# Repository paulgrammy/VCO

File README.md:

# Thomas-Henry-555-VCO
VCOs or Voltage Controlled Oscillators output a signal at a fixed amplitude but variable frequency depending on the amplitude of the input voltage. 

In Audio, VCOs are used as bases for Synths and Modular-style music that is commonly paired with the Eurorack standard. The Frequency domain of Audio is 20-20k Hz.

This repo is based on the Thomas Henry VCO: 4 Waveforms, clean 1V/Oct, Sync, PWM modulation and External FM.

# Documentation
"VCO's of different designs, can sound different from eachother despite them producing the same basic waveforms. This difference is not really that noticeable if you listen to just the basic wave outputs. It starts to become more noticeable when you start playing with the Synchronization and the Frequency Modulation inputs. That's where this VCO really shines and I think that's why it is so popular in the modular synthesizer world. With the Hard Sync and FM functions the VCO-555 produces a very full sound, rich in harmonic content and very musical sounding. And it tracks very well over the octaves. Plus it's very stable with the PTC installed for temperature compensation. You'll find out once you build this module and start experimenting with it. It's the VCO of choise for many hardened Modular Synthesizer aficionados." Source: Eddy Bergman

This project mainly used the findings from Mr. Bergman found [here](https://www.eddybergman.com/2020/12/synthesizer-build-part-37-thomas-henry.html).

# Simulation
[Falstad](https://www.falstad.com/circuit/circuitjs.html?ctz=CQAgjCAMB0l3BWEBOaB2AHAZmcjAWBLANgwCYwsRjkQl8qEBTAWjDACgw19w1i+AsMjIgy+SFHDw4UWJCQBRABoAFEADEAsiACCAF31MAdgFcAhvoCWAe2McA7uBFjIGMeNfvIHAE4feMjcAkCxIXkkwGR8nbiF+cDBROKgOILRweIFIhN4VVQAdAGdtLh5E0TI0ZLJ3LBIpKJk5LAwk6I7wkABhAHldACUAZUUOAHNBMQlJsgRs1PTM0K7JMN5ePsGRjgGKsWq92fnJabAkSQvoBB29+qEk0IRRC5BptnOpGGv-JLqusk8a0a0T84FqrzAAgB60hUnqIN27FE+Hw7iRr2IESkbzOnzk10RD1avHRJG82MiH0u10WsPwsJOdM0AEkAHKjbgkokEMHuFHkprwOSIFnsxwhelQwErcXQiFS3hPbyguVK3l0cGREGxcFq9Fqny0gQGjV88AANWKAHpir1ugAVFWeNWqlxakHmfbIzGhHn4H1opDvaTREBoWBkTFVNCQAFYTDiVgZd3wWXTfliOavVGpJxHbPufMSC4qrPF33rWSSIJwWVlnNVZE5mJe14Yatl9upCZFrv5hAPEtOYmvWQj-0RMq8cc+8sIFHAy54AedGQQc0gK0gO32kD23xWAC2oJHc1WXTPcOQPh7B3ngTvxBeLbnDwndEH4vfA+9vGInhfZABGIMsgNCBoWzVMllmnUhcxg0I4KBfMfH8ZCsxHFDXhjFtMMBHkUlQitJiBQjwAQWsJlIhJkOCEs0II3IuzIwUfF2VEcgEfAwLIk5KTxL4OAkJtCyzS98wgSBiikooJGKd5pMUoovigJS5KKM4lJklSZLAeSzmgLAEGwBA8ExekKEjaSriwWYznEGNUTwBRiiaYoABMmAAM3MUwABt9FUjT5K+WyByefBHIwZyEGsogASffAAXYYh-wwNBXLgDzvN8gKgr05S4tsyNwmSyE0oyjSsqKTyfP8wLdP0sBoGcoyEH4UzanqSrQoBdqMGwVpryqTKZNq3KGtc-T8HQBRxGQBA5nECR0v06AkqwShFshapCDOZBRuyuq8pktgir62phDAJK3GEEKbOEZA0FwZ60rAVaqrGnL6qCs7CqKFhQse56nqAy6PrcmrvpO-TiiqaB0rONxIsxN78Hu+LZku5BrqCNoDs+o6Jt+gqYGugdyBjLBIrITbqawe7roW4g0GqenIHjPAGcJqHjsmgHScZ7i5lZ2mGA557sEO3nidOgqZqjYgwh4SAQPF7nAegcn3qqDmabphhpfGn7Gv+oHcDIZAbqINpKsh42YeCgHeoc-gGEwf08CKx7Let1puCN6H+YKlhaZarnMCSJ8ojQAPlJs6FWcxeMCBoDBA75-KlLYFrFpwanISAln-2IDPZam-6c9IeLhFS9L3ci1h055h39HFPD1lskIXy7uUGEqAb4P7sRB4zWplWHHl80w6ZcKn9MG1nr9F5OBsAPFe8QnahV4O3reEnH3eaIabiBDuXen0zYDPBQ8YC1bDMgSHe+iwbA4iMwjCeVsl4kZvYif4AIgqkSESAQJcS7izZEkDQhXAwBRWoqNyA402qwJIHBPRQOcKINATxsEoHIiAYMrFZBRFgP+Cm6QSrIE2tIchkZ3rYGWmELoJC0yr0LOmBk7D5QSm4U4f8gQsyCMmC2ERKQsGEQ4AAY2oDfYRN9B7VmgGQVgtAyGqwYQNWyKIWERHkJwCYIjD4iKfkfKEg897nzEQcPG1BbFLwEQ4yQ1RqyOLDHBcQLi4LCGeOKfgaIXC4OSG6fxQQpguPCYAlsriIkeM4c-AJ+CcYhL8Z6FJXgUAuDseooMuISFanofSdqUQlazAUHQzRlDIDVCfDQiAbCnAZLlNFHeLZWkhA6Y2VI-gukHCYa2FMRE+miA6dY1wqZelgW6RbQZEzaxNOyQcWZdi2IgAGd0toUJ34UkIc+K4d8xkNDGXg+iWTKgHCiIPbp1ZJnSGuZctwdRgE1n-lc55QgnmPGePBd5rZKALhuRwXo4BqYPmSCQasOzDQ1NBYC04tkEmvD3AMZkuhWQAHEAAyoxFkXNELM8sLZXSiDVJ1XeuoXBqmCfBbpm8gSb1wheBcDLL4+ECtBUxcFwFSDYMKeAkYJArWpjQHgkYeSaxRoQGpeByAohoCGEArcOCBXfCItVWYIB8soAjZ6ZxUTCGpk8SAWrerGs2hzSgIFnqKuVU4Di1BQLASzC+WEPLh48p7qId1OZPWgklI6risJYnVleTI3hsTz4hvAGg5RmJwjU1wVEdqaBWj8s4MOBokaGikAnuBYCg9z5+rQjmh53qlHkQRK2XNV9qAVr4kQ3E+zrjDm5Yo9wIj-4mPbdQWeqR3IRvCafMM4TRDKs5K8MCsTh1JKGZcWmutVwCpAAACQ0HuA8x4nA-jDHg6lpy74zr9GBdsz4MH5viRGuCgZG1IAKUQmAMhBXhDcCKp6SVSBYkacRd1bqXVfmDXBANIb25ZqiVmg9VEugewQqez4oHnVnzwcWi9sTunRoKbKA4sTfEjpLBOiRg9cM0rnfypAWK2SaB0AYIwZhLC2HsLIwjaIEjxqkGQLWuAuPcZ4xgJM-LIA8aE7gJ4yYDHigkacB4bGYUZDdX2tjvAKOsmKKUCYKQaUabgs-IEMGo08kAgIAZQIBkfy6AQJFFnFyplkV49ZXcUimdeOgWN6b00SYSAM9EpmVWTqM13S8TmtXXXDlxogJrUSUyoI+mQhA5glNSvOSgqbFq2qDhwAdw6BonBPb3JV6WJhZa7FlsCJYJiBZzIF0rF9JBbLoJfODkEGuyEvDBoirWeStfCScHCNwuuSFaysXZTbPgHIEcENjT53B1bEcEOrgXuG7GnbISNBnhtUnxHfGl5KaVTfg04GD744PvnabII7sgZPijg5Nib7ioLXq7tBdpj2HvIlK1druR71jvYEWJcEe2DTigB-94IRk-HjbqHgyNB6DtRKh1E7rQPghqgB2ypH7hLxscvGI6Y5K2NWZ8LImtePB6dpjSwWgqBhPCfOOJgRlignhPJf-GtIjWcuvgopn0bHrFA+mOfDAPpedOEF9OY5s5mxXYl+4DJGZZsY8vgD0Jv3jSK9x2jgRuOXBK-B72k43Oyw+lk0sJzAzeArsGAAEWKEMAAmqybooJ8c5hpQTkMqYDt4Ks67qsoIfeSBrY1ytdz-e7pwcAzD-hQ91aD9+0XcjeDx8a1d2EcGk++4nbExyl7U3zBIfiXAS74AQAGLoLQ6huh2GMEwaRgV9xHhuDB7PcHs8vBxBtwSS3wnZ570NhtI3qQ3EDxd-pVZdnBmbee13AYZ+J8IcQjoD75ACqqBRaKltWYmrCHn7U6zZ978T77iYruuyu+q8S6YVm7M+eHOZnMJmu4+HSW+H0hLX-z-yYvmLsZLaLQoP6eMFmcgCCZfAEaoLZA1AEOAeBNEEEXpbnTwePOXd3FsWXLsDJRlUEDAhcDJMnVicUXAxAhAycfwbA3gWZRlFAggqlHAlwE7LAugn0GOX8azCTGpFggFdYI3NIWFTg14BzRFfg5EEAUvcvYFOFLgkkSFDELEVAug0hdg0cZ+ZgpQ6QA4TtISWMaQLMTTSEdwTTIKGSdSBSM2OKQw4odSTSUw+Oc4CuNgLAFRGMK2ecUgJWDmWMOKaKQTdsbAcgE1VmdGFuIOLOZ2OBa8ZyXwoIbgHgTwgafuFw6mAgO6IIzOU2bSOBOIsKAA1EekAme2YI02ewhGBQHAFEbgcePAAmL4fGZwtoX2J8GpMuE2OwnVaKdsVobeH-WOMgOKAcdgTaEQHGf0Z6bmfI1I2GGw-GaKPo+MSFSgDGW2EVZBdqSLZuMY8uAWbOao7gJY3-HgAaNY6qVuEmOGcMKBOYTkZwumZuTWYyYQaY-o3PLfJox2P6L4Po26I4QgauEOd4tweKLmTaJ8UYo4goiY06P4+BWyQEyEDmF4-mP6AyYyBaIyAgX-UyWKUI7aK5JIOYb4+BAqdY5op2dIu46oICLaJWVOQk0E8Yp2W4qYlED9AcEQYgUmOBcoikoyKk-0Gkr6OkkOJILWFETAQXAJCiXATw+4pkyMFkhheEkIiE2AMIAaSgbREGCgeoEE-kjYwWf6IkgKNgibLMICAPf9JpRXLMDpP1EXMCHlDpEQZUH4aAwNEMfQ05FAoiZNRDRIZDDneEBZN0107010r0l0mlK2XgEjT0nwCdR0vDFAcEWdT0uQRsFhIvXgIYNkRQEAIYAAT0PEPCYH0F8DzI3Qb12HjNiSrL71HD2VGwJETP0J5HjKDwbQnwbNBCaHdOSBdKcxYTvm7Ps17Lm2bF+XDLwSiGmBIzYOnMnJfTDAM1nJcQIgUAEDa0HLXITJDJrTK20PXPnKtIZB6V9JwQInsnWTHPwJ+AvKsz+Td0XRbHYHh0iHeijMR1iDfO3K-I3M-Lgk0xrDD3HPUM8B3PXliC3PEUgvNLBBW0nMAptNgrNPuD9OyAkx-PPKhyXJ+EAoAtkDdwDNrERC+TvMULd37w7wOUREArvJoqN3WwEgOUCiSBPVIUtn82SHAEbWIGgBoCZlqRoHqFpmyHWmvCSBIGLn-Eljk1kGVWYs2lGQEIeHjwaUbXDHekhCCBoUIFNPjDkDqW4n9jfOvFRDvVkvSx1FYsiHYqAqfMEJUrBQP1+UcocoXFbwkxspUvEGm24J1C7C828uHN+UCq8pzB82orCocwXSCrb34knx1DgpqCnQPR+Ecuz1+BcSG0XRuAyrDFYUFTytkLrI7MHz8oGxcD4OZ3EMqoqukOZwWF4McsvEoF1EvkzOzMHMcsPj4LMSwC7K6qIy6p2UFAkzStYUcqwTsoXEkVqAD3fg8q7Bmq7CqtSoXAdT4JO3d06rWuYkcuHVWH6umuCBqp+RGvUwmuOomoAlCB4LkwEEjKkAet4FUAAHUtAPN7qFx0QHqnyXAnod5-qQFygUgHrcMhzSMYskBXrqNDATALBrA7ApxJgVCwarVrMqx1pEoi84AqA2RmR7Q0UsUQBVAABVLFEYEAF65kS3e0FdCTCqqckIdgGUWIBIFGh4FQ43WETmtQ4Qtke0YoQoIoKmmmumxENmtGlIZ8n5dsgfTbcWz5S5Nmrc2K+swfdTZW465W66oiOUQGwBQGudJ0LkLoQBZmrEQi3CcJc20Ia22MScT0aCKcjhaQS-D-My0Mb-OACQTkWOekSKekDS9Gq2rUQEcJQ29uHxe2220Oyce1Jghc98COtCcO3IV-BIaymQO+MHfc75RIPvduQ8s+KOmCjMZ2mQ12ksT0PUBcqC6YXJW9GMpfH2ngP266HgdgdsMylRe8QTbiQXH+BgT00EbLJsj8AlTUDwQM0e1ssCeM9rB4QGkRQ2qerO7dcEKIZ0Dm6OyCbereglDOjeRehIHdeeoHUC2uzwCO+OkkROhO0u++40DelWp3K+zzOejO5YWsKZe69+z5Ptd6SidZHiBcjpG25+B0tmwQiO868EWZFq2AuiG61KuB2quBz+ka2kaBr6hSlANa4msm7YEFBBlAKBnAz+nwGwKYKgSSciDSiAWnOAChdjahm6qhhyLiykeh6QflZhiASoSKNhqYdRRoCmdgOgXh2YMQaR+aIR7q0R7hxhqpUIGRwtDgIAA)

# Schematic
[555 VCO.pdf](https://github.com/user-attachments/files/27636569/555.VCO.pdf)

# PCB Designs
V1:

V2:

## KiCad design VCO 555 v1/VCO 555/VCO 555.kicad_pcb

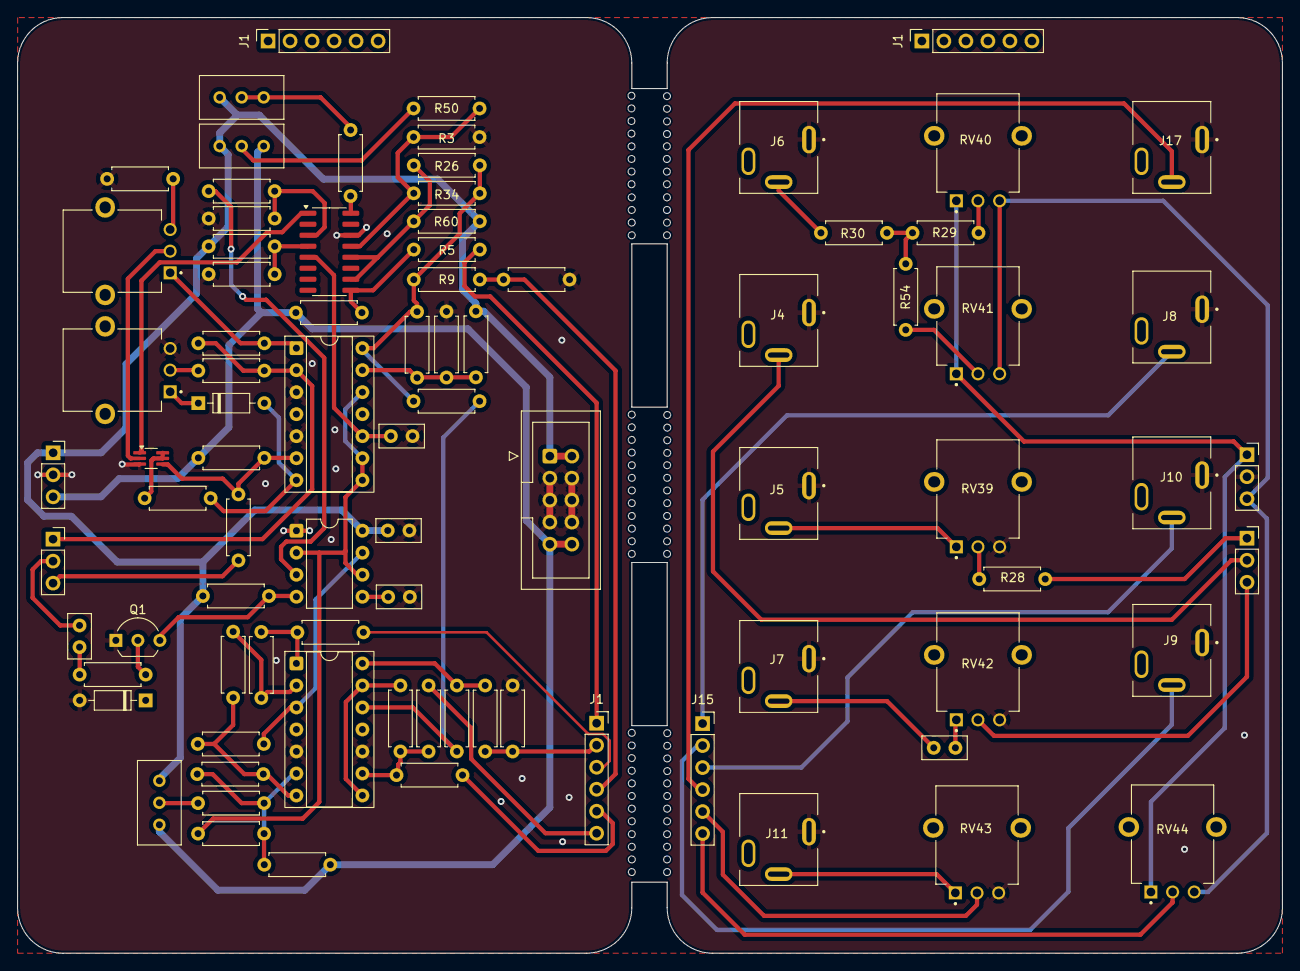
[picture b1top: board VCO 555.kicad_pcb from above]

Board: 2 copper layers, 146.0 x 108.0 mm, 104 parts (0 on the bottom side), 56 nets.

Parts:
C2: 470pF; C_Disc_D5.0mm_W2.5mm_P2.50mm
C3: 0.001uF; C_Disc_D5.0mm_W2.5mm_P2.50mm
C4: 2200pF; C_Disc_D5.0mm_W2.5mm_P2.50mm
C11: 0.1uF; C_Disc_D5.0mm_W2.5mm_P2.50mm
C12: 0.22uF; C_Disc_D5.0mm_W2.5mm_P2.50mm
D1, D2: 1N4148; D_DO-35_SOD27_P7.62mm_Horizontal
J1, J1#2, J1#3: Main Outs; PinSocket_1x06_P2.54mm_Vertical
J2: Main Power; PinSocket_1x03_P2.54mm_Vertical
J4: HARD SYNC; SAMESKY_SJ3-35052B
J5: EXP FM; SAMESKY_SJ3-35052B
J6: 1V/OCT; SAMESKY_SJ3-35052B
J7: LIN FM; SAMESKY_SJ3-35052B
J8: SINE; SAMESKY_SJ3-35052B
J9: Square; SAMESKY_SJ3-35052B
J10: RAMP; SAMESKY_SJ3-35052B
J11: PWM; SAMESKY_SJ3-35052B
J12: IDC Socket; IDC-Header_2x05_P2.54mm_Vertical
J13: Main Ins; PinSocket_1x03_P2.54mm_Vertical
J14: IO Power; PinSocket_1x03_P2.54mm_Vertical
J15: IO Outs; PinSocket_1x06_P2.54mm_Vertical
J16: IO Ins; PinSocket_1x03_P2.54mm_Vertical
J17: TRIANGLE; SAMESKY_SJ3-35052B
Q1: 2N3904; TO-92_Inline_Wide
Q2: DMMT3906W-7-F; SOT-363_SC-70-6_Handsoldering
R2, R3: 390; R_Axial_DIN0207_L6.3mm_D2.5mm_P7.62mm_Horizontal
R4, R5: 1k; R_Axial_DIN0207_L6.3mm_D2.5mm_P7.62mm_Horizontal
R6, R7: 1.5k; R_Axial_DIN0207_L6.3mm_D2.5mm_P7.62mm_Horizontal
R8: 1.8k; R_Axial_DIN0207_L6.3mm_D2.5mm_P7.62mm_Horizontal
R9, R10, R13: 2k; R_Axial_DIN0207_L6.3mm_D2.5mm_P7.62mm_Horizontal
R12: 2.2k; R_Axial_DIN0207_L6.3mm_D2.5mm_P7.62mm_Horizontal
R14, R15: 4.7k; R_Axial_DIN0207_L6.3mm_D2.5mm_P7.62mm_Horizontal
R16, R17, R18, R19, R20: 10k; R_Axial_DIN0207_L6.3mm_D2.5mm_P7.62mm_Horizontal
R21, R22: 20k; R_Axial_DIN0207_L6.3mm_D2.5mm_P7.62mm_Horizontal
R23, R27: 22k; R_Axial_DIN0207_L6.3mm_D2.5mm_P7.62mm_Horizontal
R26: 39k; R_Axial_DIN0207_L6.3mm_D2.5mm_P7.62mm_Horizontal
R28, R29, R30, R31, R32, R34, R35: 100k; R_Axial_DIN0207_L6.3mm_D2.5mm_P7.62mm_Horizontal
R33: 137k; R_Axial_DIN0207_L6.3mm_D2.5mm_P7.62mm_Horizontal
R45: 120k; R_Axial_DIN0207_L6.3mm_D2.5mm_P7.62mm_Horizontal
R46: 150k; R_Axial_DIN0207_L6.3mm_D2.5mm_P7.62mm_Horizontal
R47: 190k; R_Axial_DIN0207_L6.3mm_D2.5mm_P7.62mm_Horizontal
R48, R49, R50, R51: 1M; R_Axial_DIN0207_L6.3mm_D2.5mm_P7.62mm_Horizontal
R52: 1.5M; R_Axial_DIN0207_L6.3mm_D2.5mm_P7.62mm_Horizontal
R53: 2.2M; R_Axial_DIN0207_L6.3mm_D2.5mm_P7.62mm_Horizontal
R54: 3.3M; R_Axial_DIN0207_L6.3mm_D2.5mm_P7.62mm_Horizontal
R60: 300k; R_Axial_DIN0207_L6.3mm_D2.5mm_P7.62mm_Horizontal
R61: 5.6k; R_Axial_DIN0207_L6.3mm_D2.5mm_P7.62mm_Horizontal
RV1, RV36: 100k; TRIM_PTN091-V100115K1B
RV24: 25k; Potentiometer_Bourns_3296W_Vertical
RV37, RV38: 100k; Potentiometer_Bourns_3296W_Vertical
RV39: EXP ATTEN; TRIM_PTN091-V100115K1B
RV40: COARSE; TRIM_PTN091-V100115K1B
RV41: FINE; TRIM_PTN091-V100115K1B
RV42: LIN ATTEN; TRIM_PTN091-V100115K1B
RV43: PWN IN; TRIM_PTN091-V100115K1B
RV44: PULSE WIDTH; TRIM_PTN091-V100115K1B
TH11: 2k; R_Axial_DIN0207_L6.3mm_D2.5mm_P7.62mm_Horizontal
U1: TLC555xP; DIP-8_W7.62mm
U2: LM13700; SOIC-16_3.9x9.9mm_P1.27mm
U3, U4: TL074; DIP-14_W7.62mm_Socket
mousebites: mousebites; holes
mousebites#2, mousebites#3, mousebites#4, mousebites#5, mousebites#6, mousebites#7, mousebites#8, mousebites#9, mousebites#10, mousebites#11, mousebites#12, mousebites#13, mousebites#14, mousebites#15, mousebites#16, mousebites#17, mousebites#18: mousebites; holes

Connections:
+12V: C11.1, J2.1, J12.1, J12.2, J14.1, R15.2, R16.2, R17.1, R60.1, RV24.3, RV37.3, RV38.1, RV40.1, RV41.1, RV44.1, U1.8 (VCC)
-12V: J2.3, J12.9, J12.10, J14.3, R46.1, R52.1, R61.2, RV37.1, RV38.3, RV40.3, RV41.3, RV44.3
CLOCK: R14.1, U1.3 (Q)
GND: C3.1, C4.2, C11.2, D1.2 (A), J2.2, J4.1 (S), J5.1 (S), J6.1 (S), J7.1 (S), J8.1 (S), J9.1 (S), J10.1 (S), J11.1 (S), J12.3, J12.4, J12.5, J12.6, J12.7, J12.8, J14.2, J17.1 (S), Q1.1 (E), Q2.3 (B2), R2.1, R3.1, R6.1, R7.1, R8.1, R10.1, R21.2, RV36.3, RV39.3, RV42.3, RV43.3, U1.1 (GND), U2.14 (+), U3.3 (+), U3.5 (+), U4.5 (+), U4.10 (+)
HARD SYNC IN: C2.1, J4.2 (T), J13.2, J16.2
LIN FM IN: J13.3, J16.3, R48.1, RV42.2
MULT IN: J13.1, J16.1, R28.2, R29.1, R30.1, R51.2, R54.1, TH11.1, U3.2 (-)
unnamed: C2.2, R31.1
unnamed: C12.1, RV42.1
unnamed: D1.1 (K), Q1.2 (B), R31.2
unnamed: D2.2 (A), R23.1, U3.7
unnamed: D2.1 (K), RV36.1
unnamed: J5.2 (T), RV39.1
unnamed: J6.2 (T), R30.2
unnamed: C12.2, J7.2 (T)
unnamed: J11.2 (T), RV43.1
unnamed: Q2.2 (B1), RV1.2
unnamed: Q2.5 (E2), Q2.6 (E1), R23.2
unnamed: Q2.4 (C2), R48.2, R52.2, U3.6 (-)
unnamed: R2.2, RV1.3
unnamed: R5.2, R61.1, U2.9
unnamed: R13.1, R53.2, U4.14
unnamed: R4.1, R18.2, U4.1
unnamed: R19.1, R20.1, R33.2, U4.7
unnamed: R26.2, R60.2, U2.10, U2.12
unnamed: R27.1, RV24.1, RV24.2
unnamed: R27.2, U2.16
unnamed: R28.1, RV39.2
unnamed: R29.2, RV40.2
unnamed: R49.2, RV37.2
unnamed: R50.1, RV38.2
unnamed: R51.1, RV36.2
unnamed: R54.2, RV41.2
unnamed: RV1.1, TH11.2, U3.1
unnamed: C3.2, U1.5 (CV)
unnamed: R20.2, U1.7 (DIS), U4.3 (+)
unnamed: R3.2, R34.1, R50.2, U2.13 (-)
unnamed: R7.2, R14.2, U2.3 (+)
unnamed: R6.2, R16.1, U2.4 (-)
unnamed: C4.1, U2.5, U3.10 (+)
unnamed: R17.2, R21.1, R22.1, U3.13 (-)
unnamed: R18.1, R19.2, U4.2 (-)
unnamed: R32.2, R33.1, R46.2, R49.1, U4.6 (-)
unnamed: R35.2, R45.1, R47.2, U4.9 (-)
unnamed: R12.2, R53.1, U4.12 (+)
unnamed: R45.2, U4.8, U4.13 (-)
PITCH: Q2.1 (C1), U2.1
PULSE-WIDTH: J1#3.6, J15.6, R47.1, RV44.2
PWM IN: J1#3.5, J15.5, R35.1, RV43.2
RAMP OUT: J1#3.3, J10.2 (T), J15.3, R4.2
RESET: Q1.3 (C), R15.1, U1.4 (R)
SINE OUT: J1#3.1, J8.2 (T), J15.1, R5.1
SQUARE OUT: J1#3.2, J9.2 (T), J15.2, R8.2, R13.2
TRI: R9.1, R12.1, R22.2, R26.1, R34.2, U3.14
TRIANGLE OUT: J1#3.4, J15.4, J17.2 (T), R9.2, R10.2
TRIG: R32.1, U1.2 (TR), U1.6 (THR), U3.8, U3.9 (-), U3.12 (+)

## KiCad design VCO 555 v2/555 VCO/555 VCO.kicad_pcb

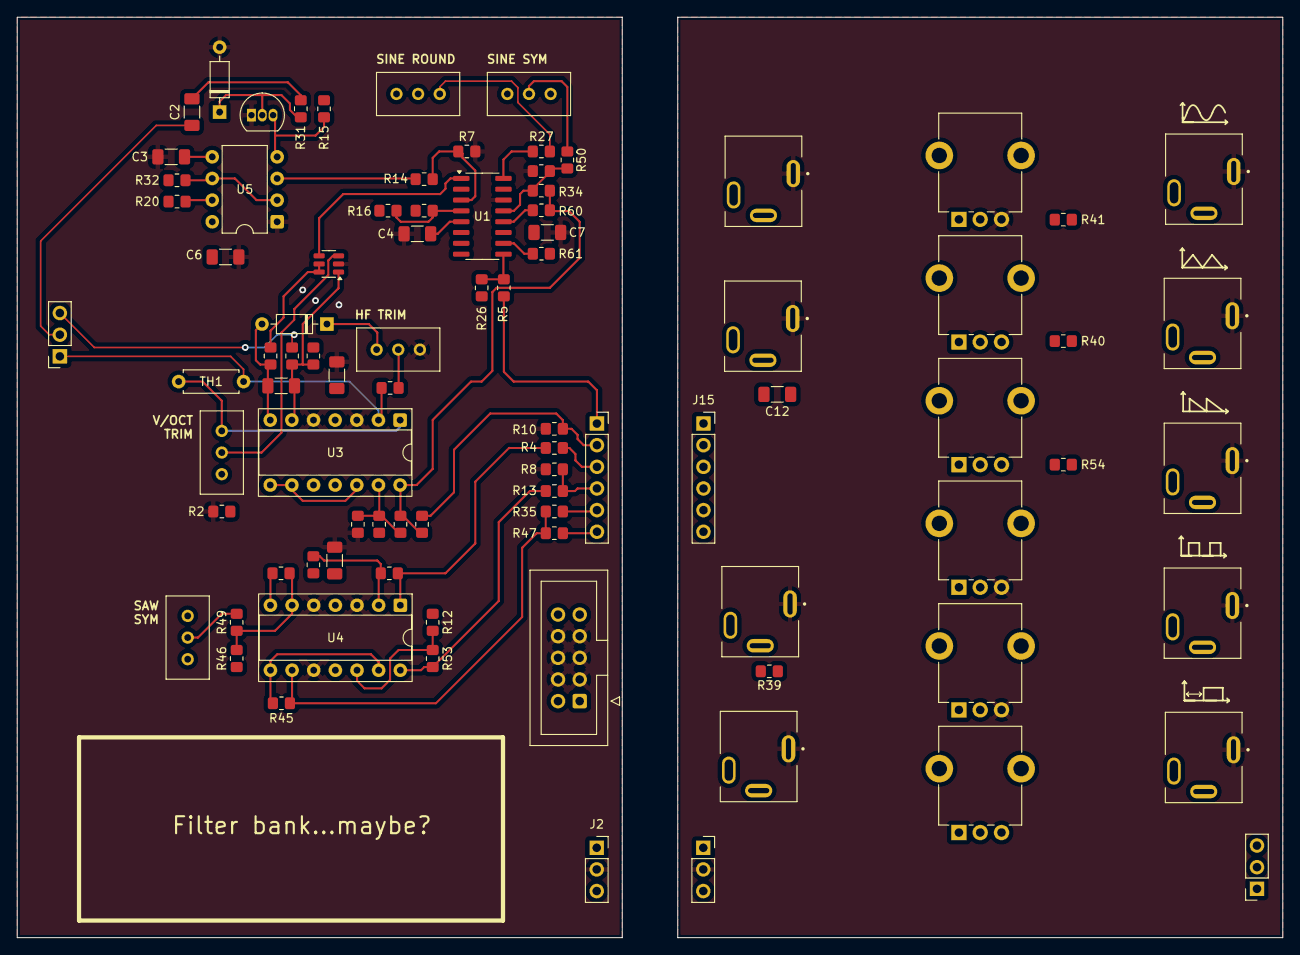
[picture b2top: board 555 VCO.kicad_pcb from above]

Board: 2 copper layers, 148.5 x 108.0 mm, 88 parts (0 on the bottom side), 66 nets.

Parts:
C1: 100pF; C_1206_3216Metric_Pad1.33x1.80mm_HandSolder
C2: 470pF; C_1206_3216Metric_Pad1.33x1.80mm_HandSolder
C3: 0.001uF; C_1206_3216Metric_Pad1.33x1.80mm_HandSolder
C4: 2200pF; C_1206_3216Metric_Pad1.33x1.80mm_HandSolder
C6, C7, C8, C9: 0.1uF; C_1206_3216Metric_Pad1.33x1.80mm_HandSolder
C12: 0.22uF; C_1206_3216Metric_Pad1.33x1.80mm_HandSolder
D1, D2: 1N4148; D_DO-35_SOD27_P7.62mm_Horizontal
J1: Main Outs; PinSocket_1x06_P2.54mm_Vertical
J2: Main Power; PinSocket_1x03_P2.54mm_Vertical
J4: HARD SYNC; SAMESKY_SJ3-35052B
J5: EXP FM; SAMESKY_SJ3-35052B
J6: 1V/OCT; SAMESKY_SJ3-35052B
J7: LIN FM; SAMESKY_SJ3-35052B
J8: SINE; SAMESKY_SJ3-35052B
J9: Square; SAMESKY_SJ3-35052B
J10: RAMP; SAMESKY_SJ3-35052B
J11: PWM; SAMESKY_SJ3-35052B
J12: IDC Socket; IDC-Header_2x05_P2.54mm_Vertical
J13: Main Ins; PinSocket_1x03_P2.54mm_Vertical
J14: IO Power; PinSocket_1x03_P2.54mm_Vertical
J15: IO Outs; PinSocket_1x06_P2.54mm_Vertical
J16: IO Ins; PinSocket_1x03_P2.54mm_Vertical
J17: TRIANGLE; SAMESKY_SJ3-35052B
Q1: DMMT5401; SOT-23-6
Q2: 2N3904; TO-92_Inline
R2, R3: 390; R_0805_2012Metric_Pad1.20x1.40mm_HandSolder
R4, R5: 1k; R_0805_2012Metric_Pad1.20x1.40mm_HandSolder
R6, R7: 1.5k; R_0805_2012Metric_Pad1.20x1.40mm_HandSolder
R8: 1.8k; R_0805_2012Metric_Pad1.20x1.40mm_HandSolder
R9, R10: 2k; R_0805_2012Metric_Pad1.20x1.40mm_HandSolder
R12: 2.2k; R_0805_2012Metric_Pad1.20x1.40mm_HandSolder
R13: 3K; R_0805_2012Metric_Pad1.20x1.40mm_HandSolder
R14, R15: 4.7k; R_0805_2012Metric_Pad1.20x1.40mm_HandSolder
R16, R17, R18, R19, R20: 10k; R_0805_2012Metric_Pad1.20x1.40mm_HandSolder
R21, R22: 20k; R_0805_2012Metric_Pad1.20x1.40mm_HandSolder
R23: 22k; R_0805_2012Metric_Pad1.20x1.40mm_HandSolder
R26: 5.6k; R_0805_2012Metric_Pad1.20x1.40mm_HandSolder
R27: R; R_0805_2012Metric_Pad1.20x1.40mm_HandSolder
R31, R32, R33, R34, R35, R39, R40, R41: 100k; R_0805_2012Metric_Pad1.20x1.40mm_HandSolder
R45: 120k; R_0805_2012Metric_Pad1.20x1.40mm_HandSolder
R46: 150k; R_0805_2012Metric_Pad1.20x1.40mm_HandSolder
R47: 330k; R_0805_2012Metric_Pad1.20x1.40mm_HandSolder
R48, R49, R50, R51: 1M; R_0805_2012Metric_Pad1.20x1.40mm_HandSolder
R52: 1.2M; R_0805_2012Metric_Pad1.20x1.40mm_HandSolder
R53: 2.2M; R_0805_2012Metric_Pad1.20x1.40mm_HandSolder
R54: 3.3M; R_0805_2012Metric_Pad1.20x1.40mm_HandSolder
R60: 39k; R_0805_2012Metric_Pad1.20x1.40mm_HandSolder
R61: 300k; R_0805_2012Metric_Pad1.20x1.40mm_HandSolder
RV1, RV4, RV37: 100k; Potentiometer_Bourns_3296W_Vertical
RV2: 100; Potentiometer_Bourns_3296W_Vertical
RV3: 25k; Potentiometer_Bourns_3296W_Vertical
RV39: EXP ATTEN; Potentiometer_Alpha_RD901F-40-00D_Single_Vertical_CircularH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
RV40: COARSE; Potentiometer_Alpha_RD901F-40-00D_Single_Vertical_CircularH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
RV41: FINE; Potentiometer_Alpha_RD901F-40-00D_Single_Vertical_CircularH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
RV42: LIN ATTEN; Potentiometer_Alpha_RD901F-40-00D_Single_Vertical_CircularH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
RV43: PWN IN; Potentiometer_Alpha_RD901F-40-00D_Single_Vertical_CircularH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
RV44: PULSE WIDTH; Potentiometer_Alpha_RD901F-40-00D_Single_Vertical_CircularH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
TH1: 2K; R_Axial_DIN0207_L6.3mm_D2.5mm_P7.62mm_Horizontal
U1: LM13700; SOIC-16_3.9x9.9mm_P1.27mm
U3, U4: TL074; DIP-14_W7.62mm_Socket
U5: TLC555xP; DIP-8_W7.62mm

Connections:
+12V: C6.1, C7.1, C8.1, C9.1, J2.1, J12.9, J12.10, J14.1, R15.2, R16.2, R17.1, R61.2, RV3.3, RV4.1, RV37.1, RV40.1, RV41.1, RV44.1, U1.11 (V+), U3.4 (V+), U4.4 (V+), U5.8 (VCC)
-12V: J2.3, J12.1, J12.2, J14.3, R26.2, R46.1, R52.1, RV4.3, RV37.3, RV40.3, RV41.3, RV44.3, U1.6 (V-), U3.11 (V-), U4.11 (V-)
/CLK: R14.1, U5.3 (Q)
/HARD_SYNC: C2.1, J13.2
/INIT_PWM: J1.6, R47.1
/LIN_FM_IN: J13.3, R48.1
/MULT_IN: J13.1, R51.2, TH1.1, U3.2 (-)
/PITCH: Q1.4 (C2), U1.1
/PWM_IN: J1.5, R35.1
/RESET: Q2.3 (C), R15.1, U5.4 (R)
/SAWTOOTH: R20.1, U5.7 (DIS)
/SAWTOOTH_OUT: J1.3, R4.2
/SINE_OUT: J1.1, R5.2
/SQUARE_OUT: J1.4, R8.1, R13.2
/TO_SINE: R9.1, R12.1, R22.2, R34.1, R60.1, U3.14
/TRIANGLE: C4.1, U1.5, U3.10 (+)
/TRIANGLE_OUT: J1.2, R9.2, R10.1
/TRIGGER: R32.1, U5.2 (TR), U5.6 (THR)
/V/OCT: Q1.3 (B2), RV2.2
GND: C3.2, C4.2, C6.2, C7.2, C8.2, C9.2, D2.2 (A), J2.2, J4.1 (S), J5.1 (S), J6.1 (S), J7.1 (S), J8.1 (S), J9.1 (S), J10.1 (S), J11.1 (S), J12.3, J12.4, J12.5, J12.6, J12.7, J12.8, J14.2, J17.1 (S), Q1.2 (B1), Q2.1 (E), R2.2, R3.2, R6.1, R7.2, R8.2, R10.2, R21.2, RV1.3, RV39.3, RV42.3, RV43.3, U1.14 (+), U3.3 (+), U3.5 (+), U4.3 (+), U4.5 (+), U4.10 (+), U5.1 (GND)
HARD SYNC IN: J4.2 (T), J16.2
LIN FM IN: J16.3, RV42.2
MULT IN: J16.1, R39.1, R40.1, R41.2, R54.1
unnamed: C2.2, R31.1
unnamed: C12.1, RV42.1
unnamed: C1.2, D1.2 (A), R23.2, U3.7
unnamed: D1.1 (K), RV1.1
unnamed: D2.1 (K), Q2.2 (B), R31.2
unnamed: J5.2 (T), RV39.1
unnamed: J6.2 (T), R39.2
unnamed: C12.2, J7.2 (T)
unnamed: J11.2 (T), RV43.1
unnamed: C1.1, Q1.1 (C1), R48.2, R52.2, U3.6 (-)
unnamed: Q1.5 (E2), Q1.6 (E1), R23.1
unnamed: R2.1, RV2.3
unnamed: R13.1, R53.2, U4.14
unnamed: R4.1, R18.2, U4.1
unnamed: R19.1, R20.2, R33.2, U4.7
unnamed: R5.1, R26.1, U1.9
unnamed: R27.1, U1.16
unnamed: R27.2, RV3.1
unnamed: R40.2, RV40.2
unnamed: R41.1, RV39.2
unnamed: R49.2, RV37.2
unnamed: R50.1, RV4.2
unnamed: R51.1, RV1.2
unnamed: R54.2, RV41.2
unnamed: R60.2, R61.1, U1.10, U1.12
unnamed: RV2.1, TH1.2, U3.1
unnamed: R3.1, R34.2, R50.2, U1.13 (-)
unnamed: R7.1, R14.2, U1.3 (+)
unnamed: R6.2, R16.1, U1.4 (-)
unnamed: U3.8, U3.9 (-), U3.12 (+)
unnamed: R17.2, R21.1, R22.1, U3.13 (-)
unnamed: R18.1, R19.2, U4.2 (-)
unnamed: R32.2, R33.1, R46.2, R49.1, U4.6 (-)
unnamed: R35.2, R45.1, R47.2, U4.9 (-)
unnamed: R12.2, R53.1, U4.12 (+)
unnamed: R45.2, U4.8, U4.13 (-)
unnamed: C3.1, U5.5 (CV)
PULSE-WIDTH: J15.6, RV44.2
PWM IN: J15.5, RV43.2
SAWTOOTH OUT: J10.2 (T), J15.3
SINE OUT: J8.2 (T), J15.1
SQUARE OUT: J9.2 (T), J15.4
TRIANGLE OUT: J15.2, J17.2 (T)

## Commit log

2026-05-12 Pulled over the projects.
2026-05-12 Removed extra folder.
2026-05-12 Renamed.
